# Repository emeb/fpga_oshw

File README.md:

# fpga_oshw
Hardware Designs for FPGA Applications

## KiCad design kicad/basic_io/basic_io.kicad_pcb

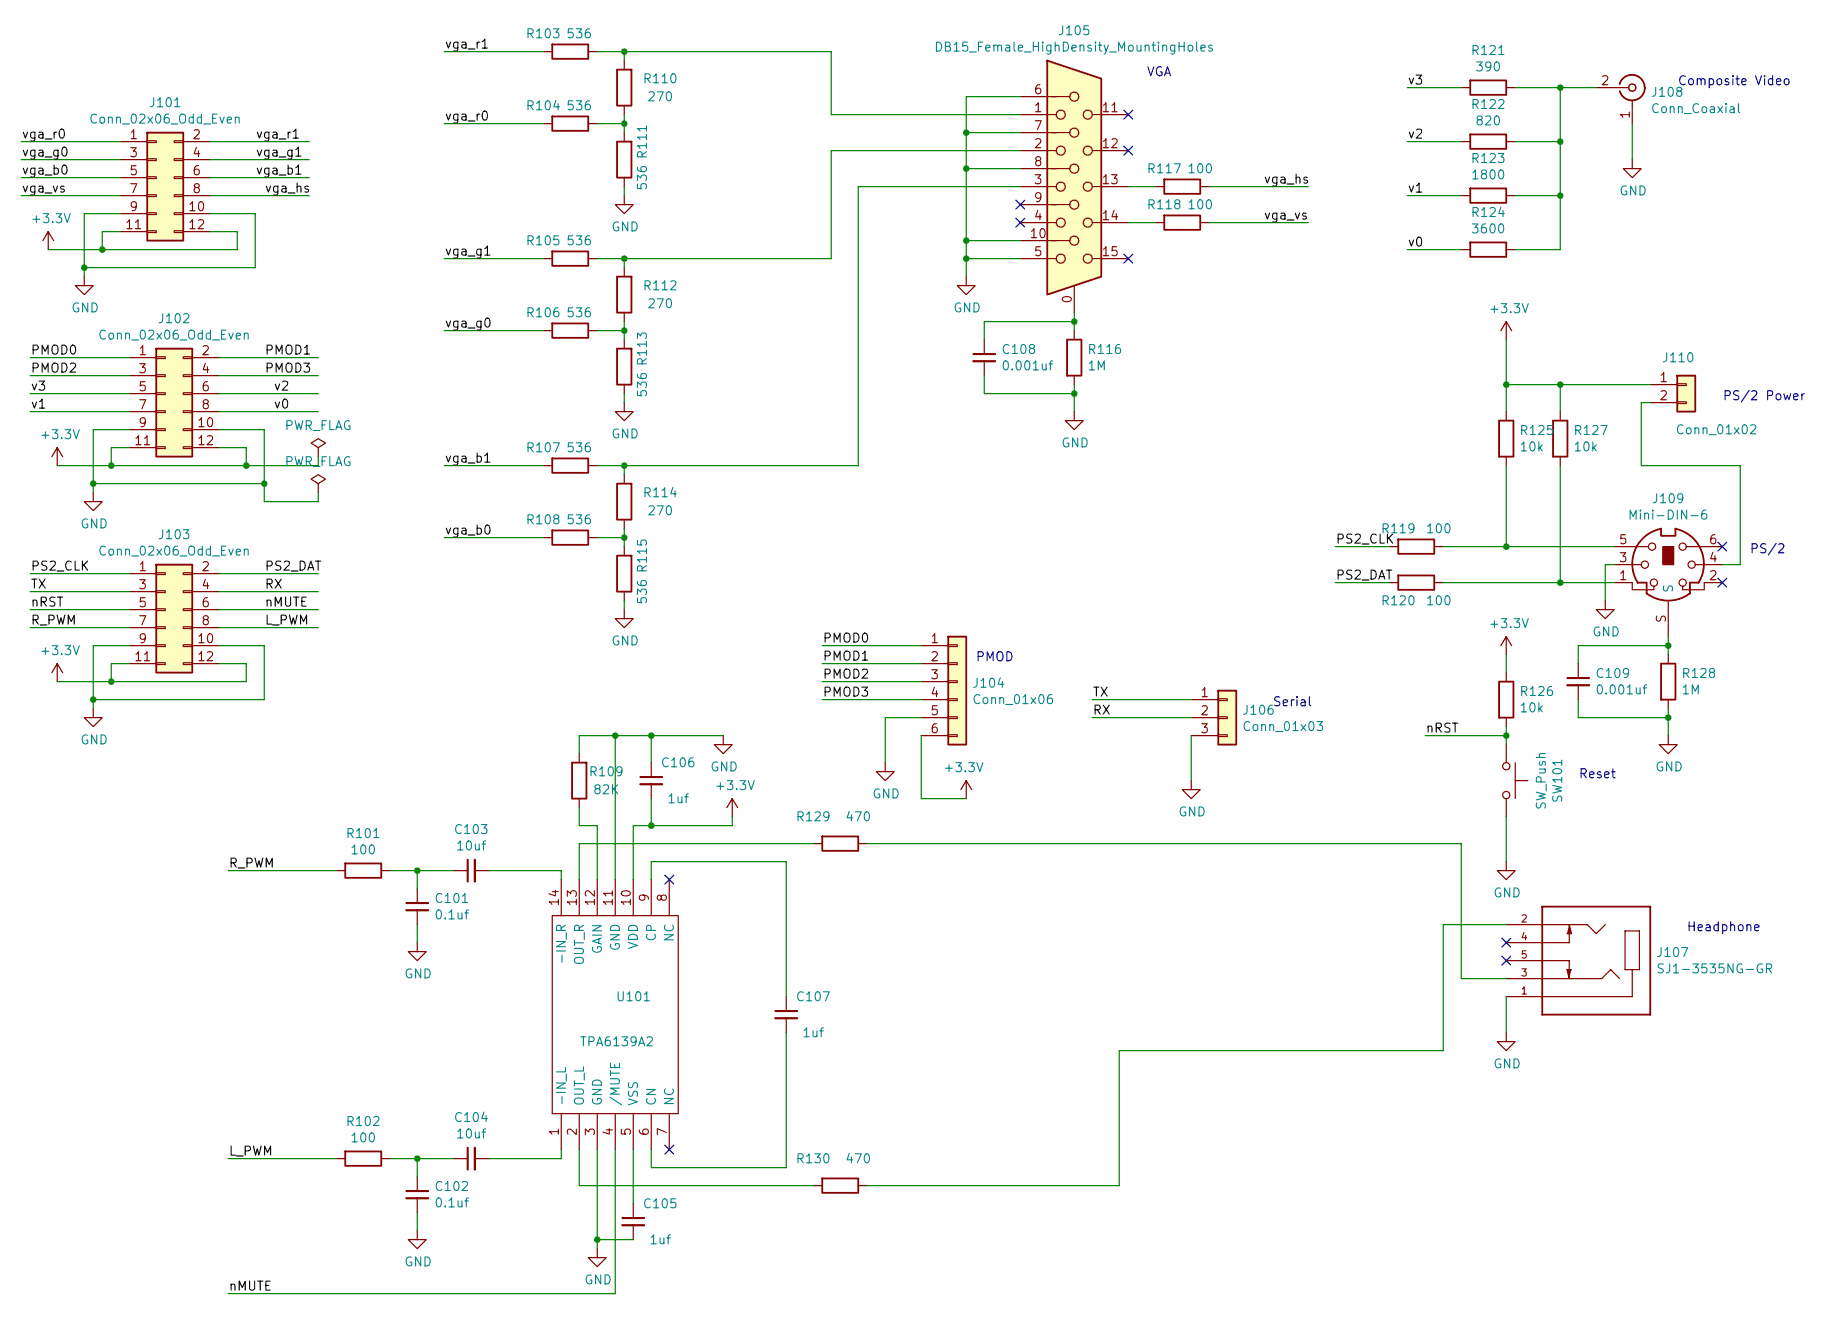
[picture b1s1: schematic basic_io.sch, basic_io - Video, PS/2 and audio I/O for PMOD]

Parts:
C101, C102: 0.1uf; C_0603_HandSoldering
C103, C104: 10uf; C_0805_HandSoldering
C105, C106, C107: 1uf; C_0805_HandSoldering
C108, C109: 0.001uf; C_0603_HandSoldering
J101, J102, J103: Conn_02x06_Odd_Even; Pin_Header_Straight_2x06_Pitch2.54mm
J104: Conn_01x06; Pin_Header_Straight_1x06_Pitch2.54mm
J105: DB15_Female_HighDensity_MountingHoles; DSUB-15-HD_Female_Horizontal_C-CD-0012
J106: Conn_01x03; Pin_Header_Straight_1x03_Pitch2.54mm
J107: SJ1-3535NG-GR; CUI_SJ1-3535NG-GR
J108: Conn_Coaxial; CUI_RCJ-044
J109: Mini-DIN-6; CUI_MD-60S
J110: Conn_01x02; Pin_Header_Straight_1x02_Pitch2.54mm
R101, R102, R117, R118, R119, R120: 100; R_0603_HandSoldering
R103, R104, R105, R106, R107, R108, R111, R113, R115: 536; R_0603_HandSoldering
R109: 82K; R_0603_HandSoldering
R110, R112, R114: 270; R_0603_HandSoldering
R116, R128: 1M; R_0603_HandSoldering
R121: 390; R_0603_HandSoldering
R122: 820; R_0603_HandSoldering
R123: 1800; R_0603_HandSoldering
R124: 3600; R_0603_HandSoldering
R125, R126, R127: 10k; R_0603_HandSoldering
R129, R130: 470; R_0603_HandSoldering
SW101: SW_Push; SW_Tactile_SPST_Angled_PTS645Vx58-2LFS
U101: TPA6139A2; TSSOP-14_4.4x5mm_Pitch0.65mm

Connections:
+3V3: C106.2, J101.11, J101.12, J102.11, J102.12, J103.11, J103.12, J104.6, J110.1, R125.1, R126.1, R127.1, U101.10 (VDD)
/L_PWM: J103.8, R102.2
/PMOD0: J102.1, J104.1
/PMOD1: J102.2, J104.2
/PMOD2: J102.3, J104.3
/PMOD3: J102.4, J104.4
/PS2_CLK: J103.1, R119.2
/PS2_DAT: J103.2, R120.2
/RX: J103.4, J106.2
/R_PWM: J103.7, R101.2
/TX: J103.3, J106.1
/nMUTE: J103.6, U101.4 (/MUTE)
/nRST: J103.5, R126.2, SW101.1
/v0: J102.8, R124.2
/v1: J102.7, R123.2
/v2: J102.6, R122.2
/v3: J102.5, R121.2
/vga_b0: J101.5, R108.2
/vga_b1: J101.6, R107.2
/vga_g0: J101.3, R106.2
/vga_g1: J101.4, R105.2
/vga_hs: J101.8, R117.1
/vga_r0: J101.1, R104.2
/vga_r1: J101.2, R103.2
/vga_vs: J101.7, R118.1
GND: C101.2, C102.2, C105.2, C106.1, C108.2, C109.2, J101.9, J101.10, J102.9, J102.10, J103.9, J103.10, J104.5, J105.5, J105.6, J105.7, J105.8, J105.10, J106.3, J107.1, J108.1 (Ext), J109.3, R109.2, R111.1, R113.1, R115.1, R116.2, R128.2, SW101.2, U101.3 (GND), U101.11 (GND)
unnamed: C101.1, C103.1, R101.1
unnamed: C102.1, C104.1, R102.1
unnamed: C103.2, U101.14 (-IN_R)
unnamed: C104.2, U101.1 (-IN_L)
unnamed: C105.1, U101.5 (VSS)
unnamed: C107.1, U101.9 (CP)
unnamed: C107.2, U101.6 (CN)
unnamed: C108.1, J105.0, R116.1
unnamed: C109.1, J109.S, R128.1
unnamed: J105.1, R103.1, R110.2
unnamed: J105.2, R105.1, R112.2
unnamed: J105.3, R107.1, R114.2
unnamed: J105.13, R117.2
unnamed: J105.14, R118.2
unnamed: J107.2, R130.1
unnamed: J107.3, R129.1
unnamed: J108.2 (In), R121.1, R122.1, R123.1, R124.1
unnamed: J109.1, R120.1, R127.2
unnamed: J109.4, J110.2
unnamed: J109.5, R119.1, R125.2
unnamed: R104.1, R110.1, R111.2
unnamed: R106.1, R112.1, R113.2
unnamed: R108.1, R114.1, R115.2
unnamed: R109.1, U101.12 (GAIN)
unnamed: R129.2, U101.13 (OUT_R)
unnamed: R130.2, U101.2 (OUT_L)

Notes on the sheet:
Reset
PS/2
Composite Video
Serial
Headphone
PS/2 Power
PMOD
VGA

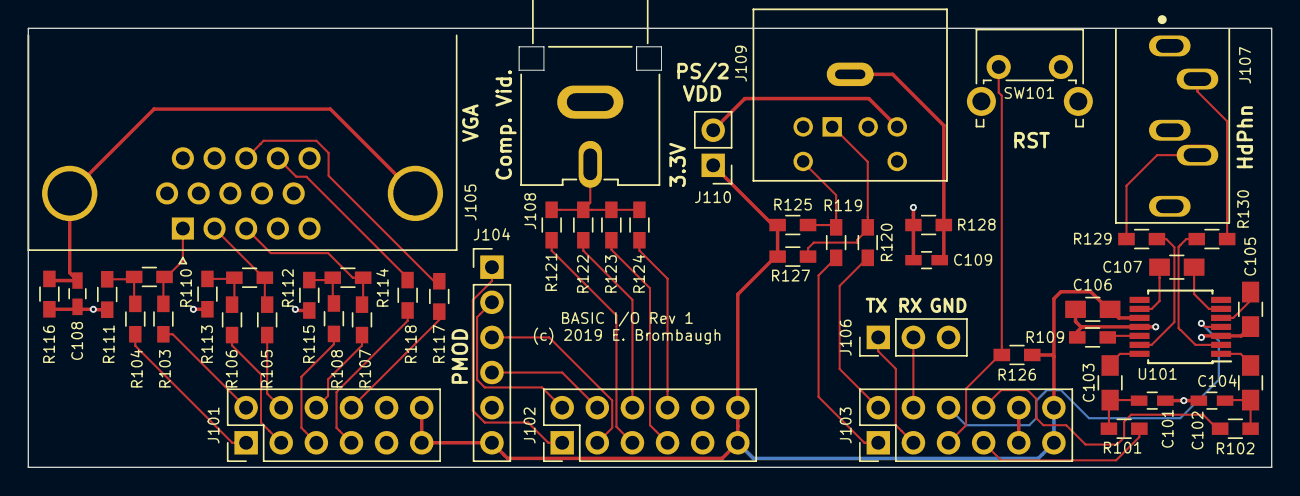
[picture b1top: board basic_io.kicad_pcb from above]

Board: 2 copper layers, 89.9 x 31.8 mm, 51 parts (0 on the bottom side), 52 nets.

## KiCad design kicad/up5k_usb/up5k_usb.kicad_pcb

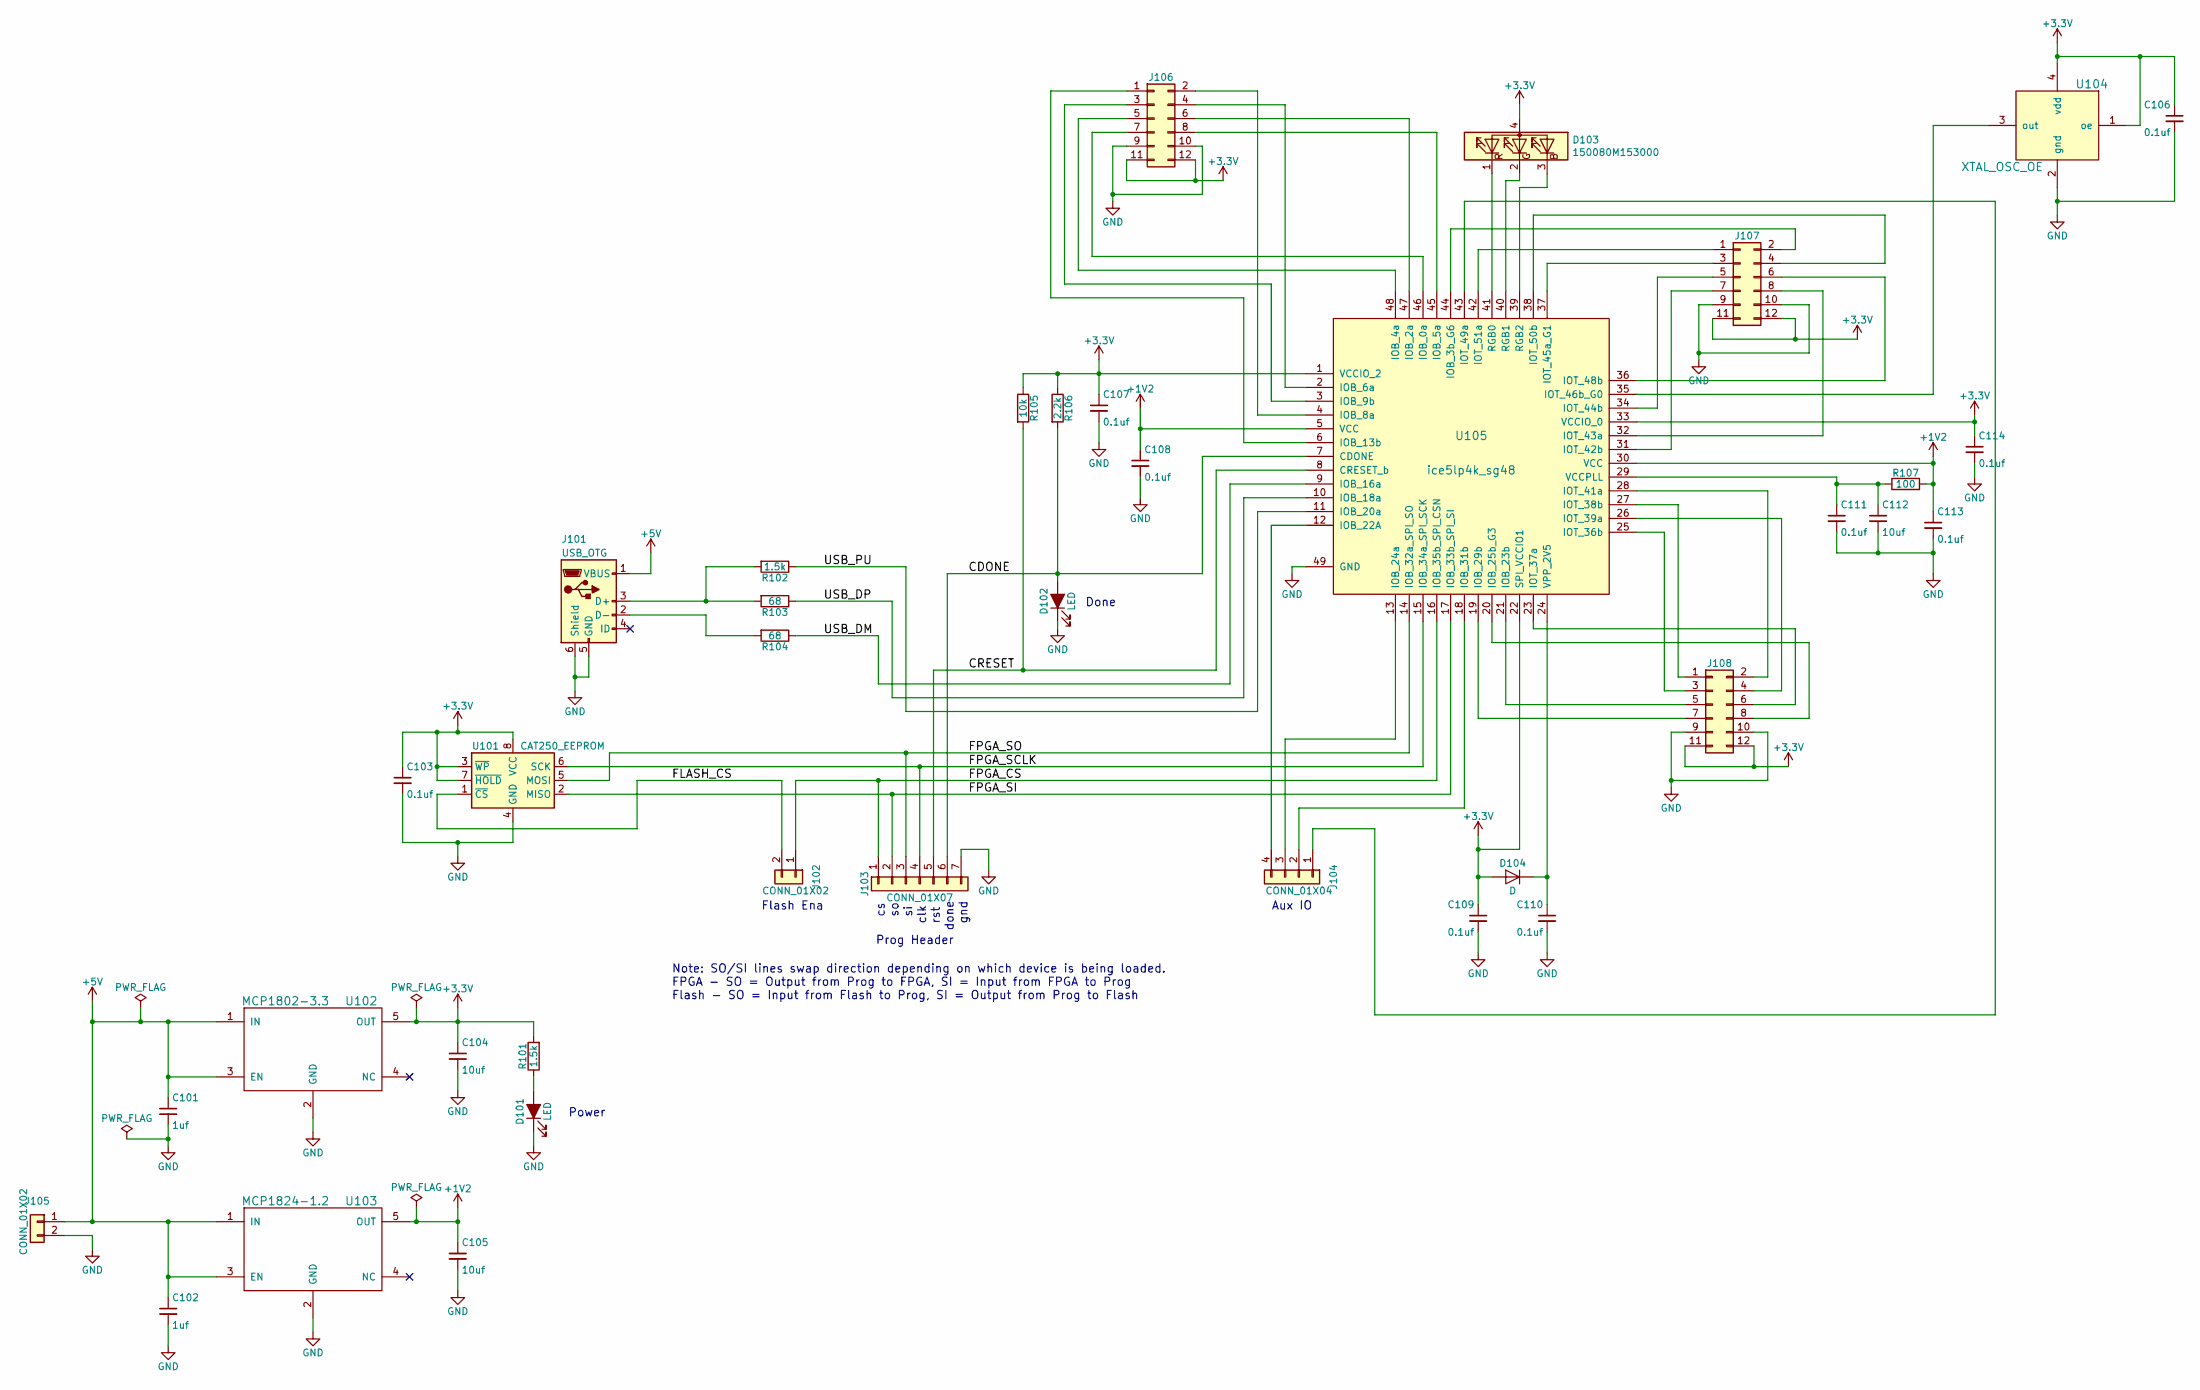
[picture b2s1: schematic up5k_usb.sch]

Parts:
C101, C102: 1uf; C_0603_HandSoldering
C103, C106, C107, C108, C109, C110, C111, C113, C114: 0.1uf; C_0603_HandSoldering
C104, C105, C112: 10uf; C_0805_HandSoldering
D101, D102: LED; LED_0603_HandSoldering
D103: 150080M153000; LED_Wurth_150080M153000
D104: D; D_0603
J101: USB_OTG; USB_Micro-B_10103594-0001LF_NoSlot
J102, J105: CONN_01X02; Pin_Header_Straight_1x02_Pitch2.54mm
J103: CONN_01X07; Pin_Header_Straight_1x07_Pitch2.54mm
J104: CONN_01X04; Pin_Header_Straight_1x04_Pitch2.54mm
J106, J107, J108: CONN_02X06; Socket_Strip_Straight_2x06_Pitch2.54mm
R101, R102: 1.5k; R_0603_HandSoldering
R103, R104: 68; R_0603_HandSoldering
R105: 10k; R_0603_HandSoldering
R106: 2.2k; R_0603_HandSoldering
R107: 100; R_0603_HandSoldering
U101: CAT250_EEPROM; SSO-8_6.8x5.9mm_Pitch1.27mm_Clearance7mm
U102: MCP1802-3.3; SOT-23-5
U103: MCP1824-1.2; SOT-23-5
U104: XTAL_OSC_OE; Crystal_SMD_Abracon_ASFL1-4pin_5.0x3.2mm
U105: ice5lp4k_sg48; QFN-48-1EP_7x7mm_Pitch0.5mm_DIY_PADS

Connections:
+1V2: C105.1, C108.1, C113.1, R107.2, U103.5 (OUT), U105.5 (VCC), U105.30 (VCC)
+3V3: C103.1, C104.1, C106.1, C107.1, C109.1, C114.1, D103.4 (A), D104.2 (A), J106.11, J106.12, J107.11, J107.12, J108.11, J108.12, R101.2, R105.1, R106.1, U101.3 (~WP), U101.7 (~HOLD), U101.8 (VCC), U102.5 (OUT), U104.1 (oe), U104.4 (vdd), U105.1 (VCCIO_2), U105.22 (SPI_VCCIO1), U105.33 (VCCIO_0)
+5V: C101.1, C102.1, J101.1 (VBUS), J105.1, U102.1 (IN), U102.3 (EN), U103.1 (IN), U103.3 (EN)
/CDONE: D102.2 (A), J103.6, R106.2, U105.7 (CDONE)
/CRESET: J103.5, R105.2, U105.8 (CRESET_b)
/FLASH_CS: J102.2, U101.1 (~CS)
/FPGA_CS: J102.1, J103.1, U105.16 (IOB_35b_SPI_CSN)
/FPGA_SCLK: J103.4, U101.6 (SCK), U105.15 (IOB_34a_SPI_SCK)
/FPGA_SI: J103.2, U101.2 (MISO), U105.17 (IOB_33b_SPI_SI)
/FPGA_SO: J103.3, U101.5 (MOSI), U105.14 (IOB_32a_SPI_SO)
/USB_DM: R104.1, U105.9 (IOB_16a)
/USB_DP: R103.1, U105.10 (IOB_18a)
/USB_PU: R102.1, U105.11 (IOB_20a)
GND: C101.2, C102.2, C103.2, C104.2, C105.2, C106.2, C107.2, C108.2, C109.2, C110.2, C111.2, C112.2, C113.2, C114.2, D101.1 (K), D102.1 (K), J101.5 (GND), J101.6 (Shield), J103.7, J105.2, J106.9, J106.10, J107.9, J107.10, J108.9, J108.10, U101.4 (GND), U102.2 (GND), U103.2 (GND), U104.2 (gnd), U105.49 (GND)
unnamed: C110.1, D104.1 (K), U105.24 (VPP_2V5)
unnamed: C111.1, C112.1, R107.1, U105.29 (VCCPLL)
unnamed: D101.2 (A), R101.1
unnamed: D103.1 (RK), U105.41 (RGB0)
unnamed: D103.2 (GK), U105.40 (RGB1)
unnamed: D103.3 (BK), U105.39 (RGB2)
unnamed: J101.2 (D-), R104.2
unnamed: J101.3 (D+), R102.2, R103.2
unnamed: J104.1, U105.43 (IOT_49a)
unnamed: J104.2, U105.18 (IOB_31b)
unnamed: J104.3, U105.13 (IOB_24a)
unnamed: J104.4, U105.12 (IOB_22A)
unnamed: J106.1, U105.6 (IOB_13b)
unnamed: J106.2, U105.4 (IOB_8a)
unnamed: J106.3, U105.3 (IOB_9b)
unnamed: J106.4, U105.2 (IOB_6a)
unnamed: J106.5, U105.48 (IOB_4a)
unnamed: J106.6, U105.47 (IOB_2a)
unnamed: J106.7, U105.46 (IOB_0a)
unnamed: J106.8, U105.45 (IOB_5a)
unnamed: J107.1, U105.42 (IOT_51a)
unnamed: J107.2, U105.44 (IOB_3b_G6)
unnamed: J107.3, U105.37 (IOT_45a_G1)
unnamed: J107.4, U105.38 (IOT_50b)
unnamed: J107.5, U105.34 (IOT_44b)
unnamed: J107.6, U105.36 (IOT_48b)
unnamed: J107.7, U105.31 (IOT_42b)
unnamed: J107.8, U105.32 (IOT_43a)
unnamed: J108.1, U105.27 (IOT_38b)
unnamed: J108.2, U105.28 (IOT_41a)
unnamed: J108.3, U105.25 (IOT_36b)
unnamed: J108.4, U105.26 (IOT_39a)
unnamed: J108.5, U105.21 (IOB_23b)
unnamed: J108.6, U105.23 (IOT_37a)
unnamed: J108.7, U105.19 (IOB_29b)
unnamed: J108.8, U105.20 (IOB_25b_G3)
unnamed: U104.3 (out), U105.35 (IOT_46b_G0)

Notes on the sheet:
clk
rst
done
gnd
Flash Ena
Aux IO
Prog Header
Power
Done
Note: SO/SI lines swap direction depending on which device is being loaded. FPGA - SO = Output from Prog to FPGA, SI = Input from FPGA to Prog Flash - SO = Input from Flash to Prog, SI = Output from Prog to Flash

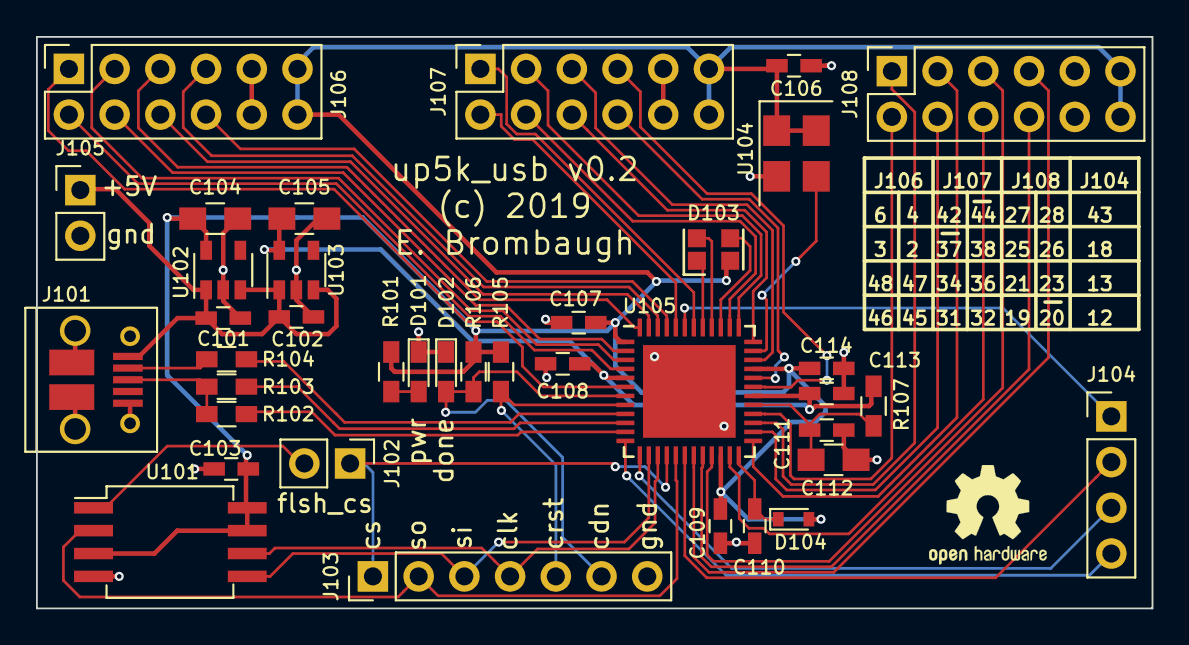
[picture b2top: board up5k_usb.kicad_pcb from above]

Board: 2 copper layers, 62.0 x 31.8 mm, 38 parts (0 on the bottom side), 51 nets.

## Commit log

2019-06-19 Initial commit of board designs

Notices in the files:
kicad/basic_io/basic_io.kicad_pcb:
(c) 2019 E. Brombaugh
kicad/up5k_usb/up5k_usb.kicad_pcb:
(c) 2019
